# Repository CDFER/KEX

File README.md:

# Currently not maintained or tested, use at your own risk

## KEX a Rapid Deployment ESP32 Board
A fast and feature-rich implementation of an ESP32 board with NeoPixel Led (WS2812B, WS2811, SK6812), I2S (Digital microphone) and I2C outputs.

## ⚙️ Features
- Supports USB C to USB C cables at 5V 3A 
- 3 Capacitive Touch Buttons
- Designed for PCB Assembly by JLCPCB 
- 3A Resettable Fuse on both the 3.3v and 5v Rails
- Programming using the CH340-c IC
- Electrostatic Discharge Protection on USB and LED Output
- Auto Reset for easy programming
- Solder Pad connections with Strain relief slots 
- High-Speed Bi-Directional Level shifted I2S and I2C ports using BSS138 like [Adafruit](https://www.adafruit.com/product/757)
- Cuttable solder pads to select between 3.3v and 5v level shifting
- LED indicators on all outputs and inputs
- Easy soldering of led strips directly to the PCB with Strain Releaf slots

## 📲 Quickstart
1. Solder the ESP32 to the footprint on the PCB

2. Connect up to 120 NeoPixels (WS2812B, WS2811, SK6812) to the output pads (IO2). 
3. Install the CH340 Drivers from [Sparkfun](https://learn.sparkfun.com/tutorials/how-to-install-ch340-drivers/all)
4. Flash the software to your ESP module! There are two options for this step:
  
&nbsp;&nbsp;&nbsp;&nbsp;&nbsp;&nbsp;[I just want to use WLED! (install release binary)](https://install.wled.me/)

&nbsp;&nbsp;&nbsp;&nbsp;&nbsp;&nbsp;[I want to modify WLED (compile from source code)](https://kno.wled.ge/advanced/compiling-wled/)

&nbsp;&nbsp;&nbsp;&nbsp;&nbsp;&nbsp;If set up correctly, the first thirty LEDs will light up!

5. Use a Computer/Phone to connect to the Wife named: WLED-AP using the password wled1234.

6. Click on the cog icon to edit settings like connecting the module to your home WiFi.
7. Upload Config File (Coming soon...)

## 💾 Pinout
Pin | IO2 | IO4 | IO14 | IO15 | IO21 | IO22 | IO27 | IO32 | IO33 | IO36
--- | --- | --- | --- |--- |--- |--- |--- |--- |--- |---
Usage | LED Output | Down Touch Pad | SCK | WS | SDA | SCL | Middle Touch Pad | SD |  Up Touch Pad | Analog Input 
LED | Yellow | | White | White | Red | Green | | White | | |
Level Shifted | | |✅|✅|✅|✅| |✅| 

## ✌️ Other

[Licensed under the MIT license](https://github.com/git/git-scm.com/blob/main/MIT-LICENSE.txt)

Designed by Chris Dirks (@CD_FER)

You can also send me emails to [cdirksfer@gmail.com](mailto:dev.cdirksfer@gmail.com), but please only do so if you want to talk to me privately.

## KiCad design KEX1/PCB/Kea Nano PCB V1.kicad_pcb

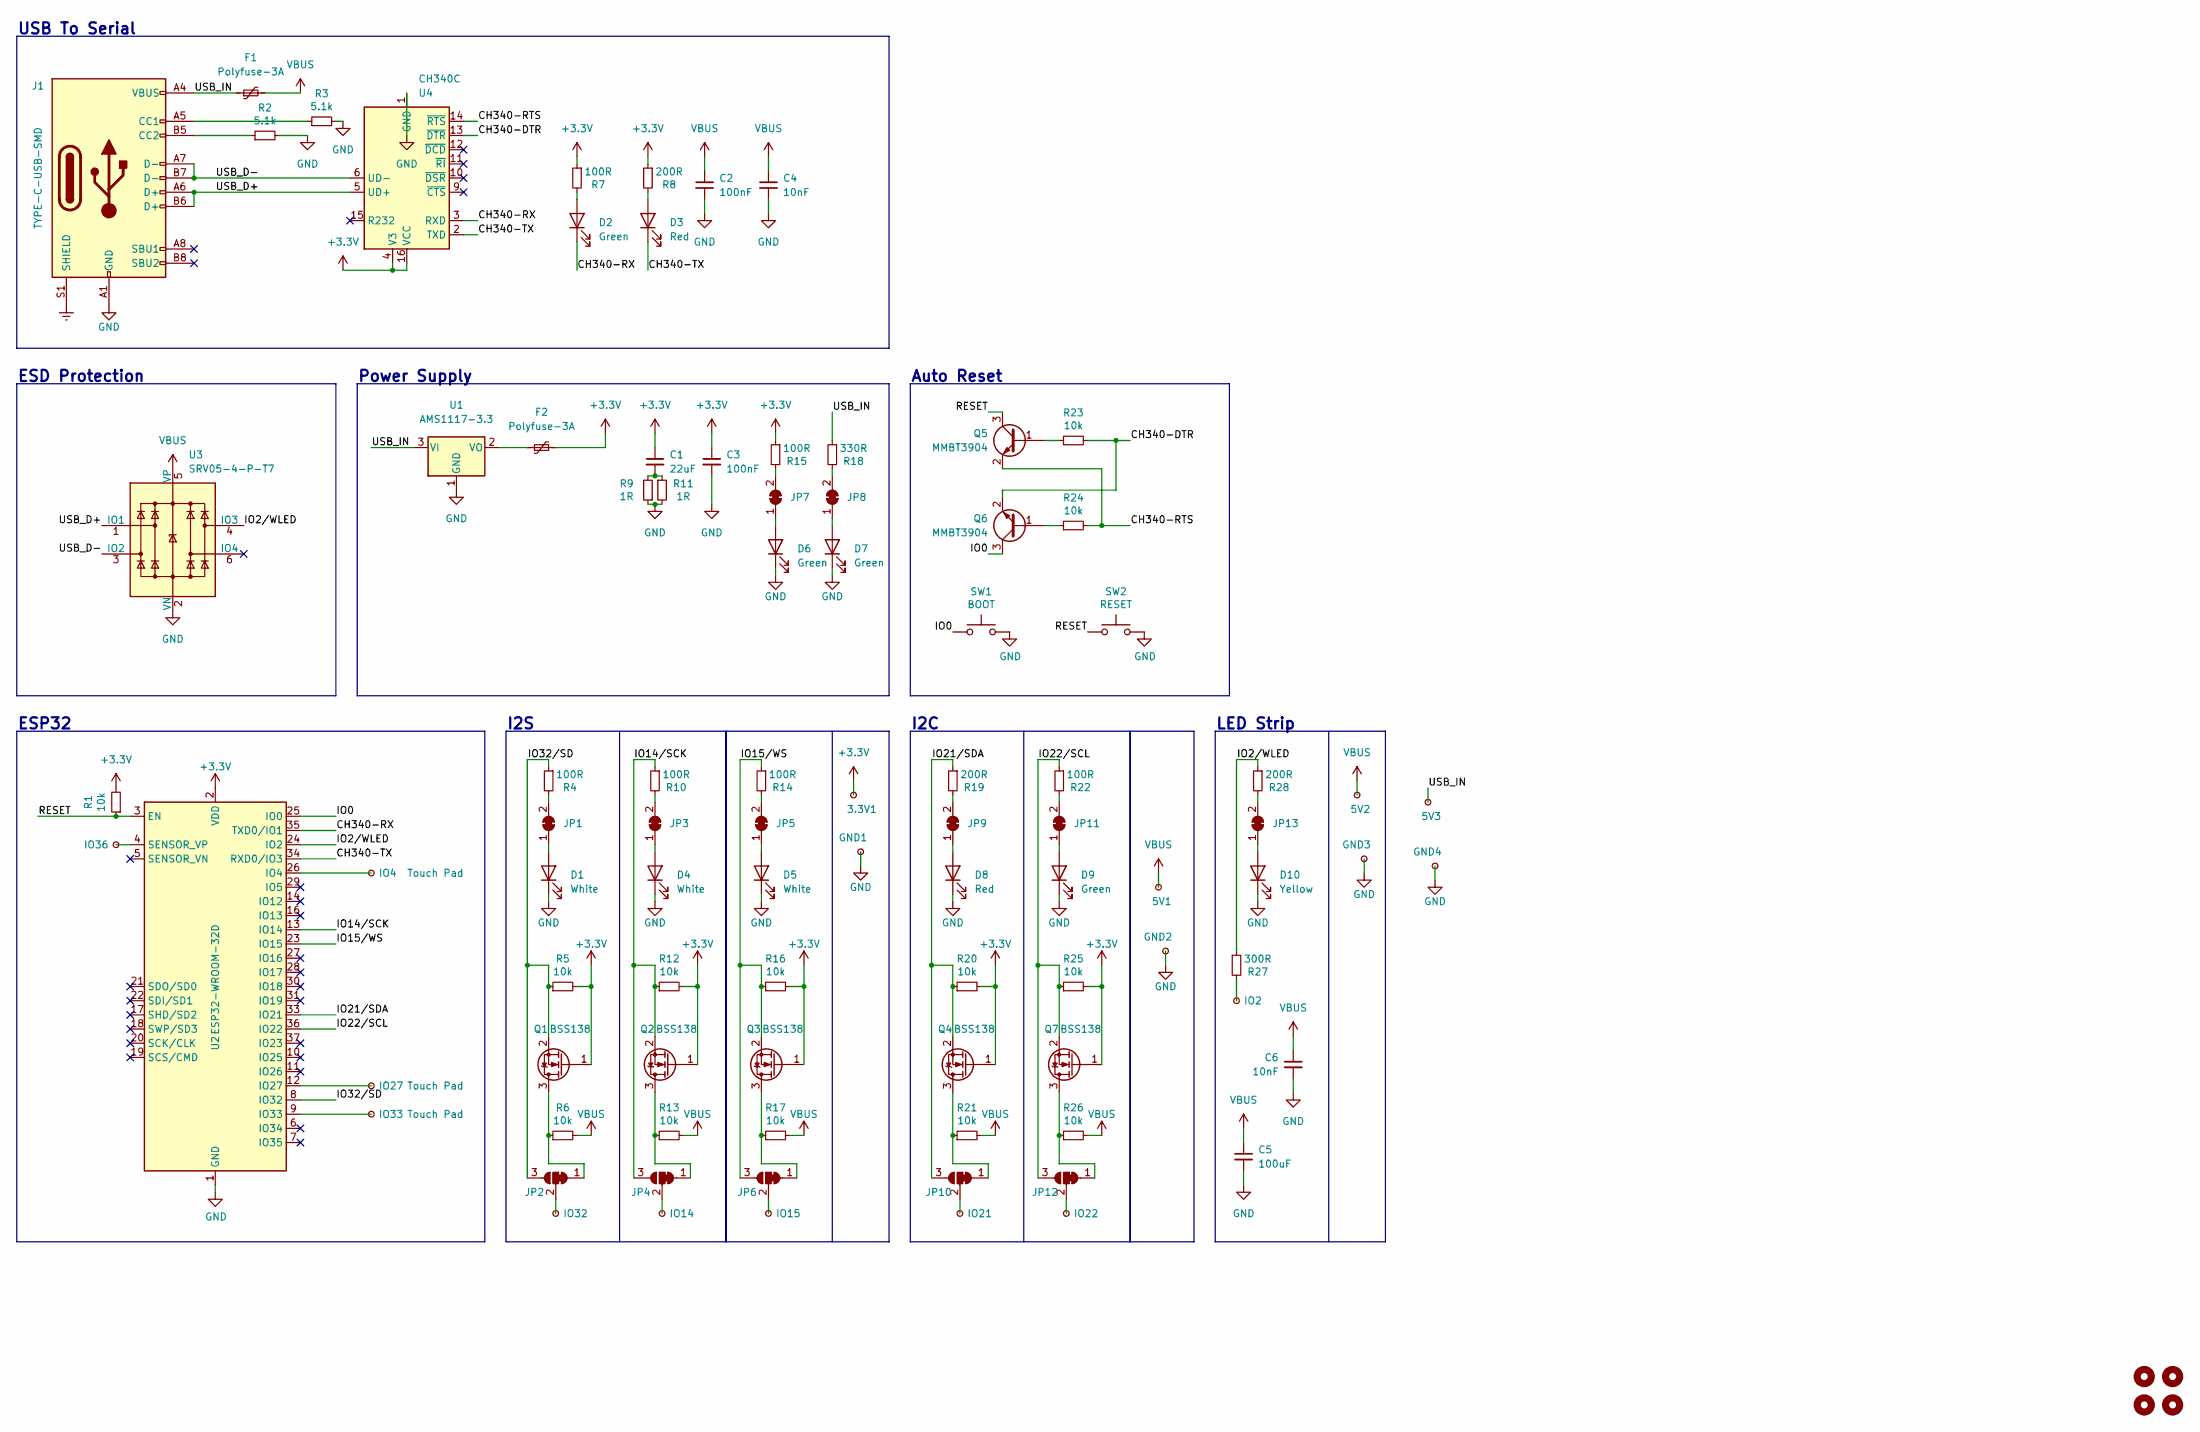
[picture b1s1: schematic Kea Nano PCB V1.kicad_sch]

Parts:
3.3V1, 5V1, 5V2, 5V3: IO; IO Pad
C1: 22uF; C_1206_3216Metric; LCSC C5672
C2, C3: 100nF; C_0402_1005Metric; LCSC C1525
C4, C6: 10nF; C_0402_1005Metric; LCSC C15195
C5: 100uF; C_1206_3216Metric; LCSC C15008
D1, D4, D5: White; LED_0603_1608Metric; LCSC C2290
D2, D6, D7, D9: Green; LED_0603_1608Metric; LCSC C72043
D3, D8: Red; LED_0603_1608Metric; LCSC C2286
D10: Yellow; LED_0603_1608Metric; LCSC C72038
F1, F2: Polyfuse-3A; Fuse_1206_3216Metric; LCSC C516068
GND1, GND2, GND3, GND4: IO; IO Pad
H1, H2, H3, H4: MountingHole; MountingHole_3.2mm_M3_DIN965
IO2, IO14, IO15, IO21, IO22, IO32, IO36: IO; IO Pad
IO4: Touch Pad; Touch Pad ST
IO27, IO33: Touch Pad
J1: TYPE-C-USB-SMD; USB_C_Receptacle_XKB_U262-16XN-4BVC11; LCSC C167321
JP1, JP3, JP5, JP7, JP8, JP9, JP11, JP13: SolderJumper_2_Bridged; SolderJumper-2_P1.3mm_Bridged_RoundedPad1.0x1.5mm
JP2, JP4, JP6, JP10, JP12: SolderJumper_3_Bridged12; SolderJumper-3_P1.3mm_Bridged12_RoundedPad1.0x1.5mm
Q1, Q2, Q3, Q4, Q7: BSS138; SOT-23; LCSC C78284
Q5, Q6: MMBT3904; SOT-23; LCSC C20526
R1, R5, R6, R12, R13, R16, R17, R20, R21, R23, R24, R25, R26: 10k; R_0402_1005Metric; LCSC C25744
R2, R3: 5.1k; R_0402_1005Metric; LCSC C25905
R4, R7, R10, R14, R15, R22: 100R; R_0402_1005Metric; LCSC C25076
R8, R19, R28: 200R; R_0402_1005Metric; LCSC C25087
R9, R11: 1R; R_0402_1005Metric; LCSC C25086
R18: 330R; R_0402_1005Metric; LCSC C25104
R27: 300R; R_0402_1005Metric; LCSC C25102
SW1: BOOT; TS-1187A-B-A-B; LCSC C318884
SW2: RESET; TS-1187A-B-A-B; LCSC C318884
U1: AMS1117-3.3; SOT-223; LCSC C6186
U2: ESP32-WROOM-32D; ESP32-WROOM-32
U3: SRV05-4-P-T7; SOT-23-6; LCSC C85364
U4: CH340C; SOP-16_3.9x9.9mm_P1.27mm; LCSC C84681

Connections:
+3V3: 3.3V1.1, C1.1, C3.1, F2.2, Q1.1 (G), Q2.1 (G), Q3.1 (G), Q4.1 (G), Q7.1 (G), R1.2, R5.2, R7.1, R8.1, R12.2, R15.1, R16.2, R20.2, R25.2, U2.2 (VDD), U4.4 (V3), U4.16 (VCC)
/CH340-DTR: Q6.2 (E), R23.2, U4.13 (~DTR)
/CH340-RTS: Q5.2 (E), R24.2, U4.14 (~RTS)
/CH340-RX: D2.1 (K), U2.35 (TXD0/IO1), U4.3 (RXD)
/CH340-TX: D3.1 (K), U2.34 (RXD0/IO3), U4.2 (TXD)
/IO0: Q6.3 (C), SW1.1, U2.25 (IO0)
/IO2/WLED: R27.1, R28.1, U2.24 (IO2), U3.4 (IO3)
/IO14/SCK: JP4.3 (B), Q2.2 (S), R10.1, R12.1, U2.13 (IO14)
/IO15/WS: JP6.3 (B), Q3.2 (S), R14.1, R16.1, U2.23 (IO15)
/IO21/SDA: JP10.3 (B), Q4.2 (S), R19.1, R20.1, U2.33 (IO21)
/IO22/SCL: JP12.3 (B), Q7.2 (S), R22.1, R25.1, U2.36 (IO22)
/IO32/SD: JP2.3 (B), Q1.2 (S), R4.1, R5.1, U2.8 (IO32)
/RESET: Q5.3 (C), R1.1, SW2.1, U2.3 (EN)
/USB_D+: J1.A6 (D+), J1.B6 (D+), U3.1 (IO1), U4.5 (UD+)
/USB_D-: J1.A7 (D-), J1.B7 (D-), U3.3 (IO2), U4.6 (UD-)
/USB_IN: 5V3.1, F1.1, J1.A4 (VBUS), J1.A9 (VBUS), J1.B4 (VBUS), J1.B9 (VBUS), R18.1, U1.3 (VI); also elsewhere on the board
GND: C2.2, C3.2, C4.2, C5.2, C6.2, D1.1 (K), D4.1 (K), D5.1 (K), D6.1 (K), D7.1 (K), D8.1 (K), D9.1 (K), D10.1 (K), GND1.1, GND2.1, GND3.1, GND4.1, J1.A1 (GND), J1.A12 (GND), J1.B1 (GND), J1.B12 (GND), R2.2, R3.2, R9.1, R11.2, SW1.2, SW2.2, U1.1 (GND), U2.1 (GND), U2.15 (GND), U2.38 (GND), U2.39 (GND), U3.2 (VN), U4.1 (GND)
unnamed: C1.2, R9.2, R11.1
unnamed: D1.2 (A), JP1.1 (A)
unnamed: D2.2 (A), R7.2
unnamed: D3.2 (A), R8.2
unnamed: D4.2 (A), JP3.1 (A)
unnamed: D5.2 (A), JP5.1 (A)
unnamed: D6.2 (A), JP7.1 (A)
unnamed: D7.2 (A), JP8.1 (A)
unnamed: D8.2 (A), JP9.1 (A)
unnamed: D9.2 (A), JP11.1 (A)
unnamed: D10.2 (A), JP13.1 (A)
unnamed: F2.1, U1.2 (VO)
unnamed: IO2.1, R27.2
unnamed: IO4.1, U2.26 (IO4)
unnamed: IO14.1, JP4.2 (C)
unnamed: IO15.1, JP6.2 (C)
unnamed: IO21.1, JP10.2 (C)
unnamed: IO22.1, JP12.2 (C)
unnamed: IO27.1, U2.12 (IO27)
unnamed: IO32.1, JP2.2 (C)
unnamed: IO33.1, U2.9 (IO33)
unnamed: IO36.1, U2.4 (SENSOR_VP)
unnamed: J1.A5 (CC1), R3.1
unnamed: J1.B5 (CC2), R2.1
unnamed: JP1.2 (B), R4.2
unnamed: JP2.1 (A), Q1.3 (D), R6.1
unnamed: JP3.2 (B), R10.2
unnamed: JP4.1 (A), Q2.3 (D), R13.1
unnamed: JP5.2 (B), R14.2
unnamed: JP6.1 (A), Q3.3 (D), R17.1
unnamed: JP7.2 (B), R15.2
unnamed: JP8.2 (B), R18.2
unnamed: JP9.2 (B), R19.2
unnamed: JP10.1 (A), Q4.3 (D), R21.1
unnamed: JP11.2 (B), R22.2
unnamed: JP12.1 (A), Q7.3 (D), R26.1
unnamed: JP13.2 (B), R28.2
unnamed: Q5.1 (B), R23.1
unnamed: Q6.1 (B), R24.1
VBUS: 5V1.1, 5V2.1, C2.1, C4.1, C5.1, C6.1, F1.2, R6.2, R13.2, R17.2, R21.2, R26.2, U3.5 (VP); also elsewhere on the board

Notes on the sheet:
ESP32
I2C
USB To Serial
ESD Protection
I2S
LED Strip
Auto Reset
Power Supply

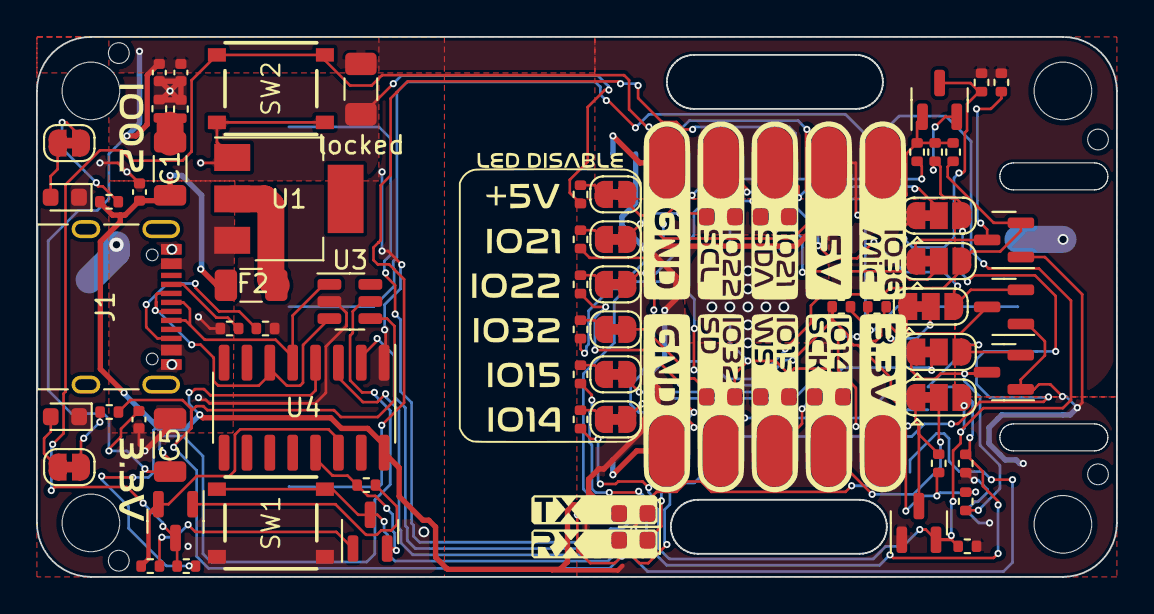
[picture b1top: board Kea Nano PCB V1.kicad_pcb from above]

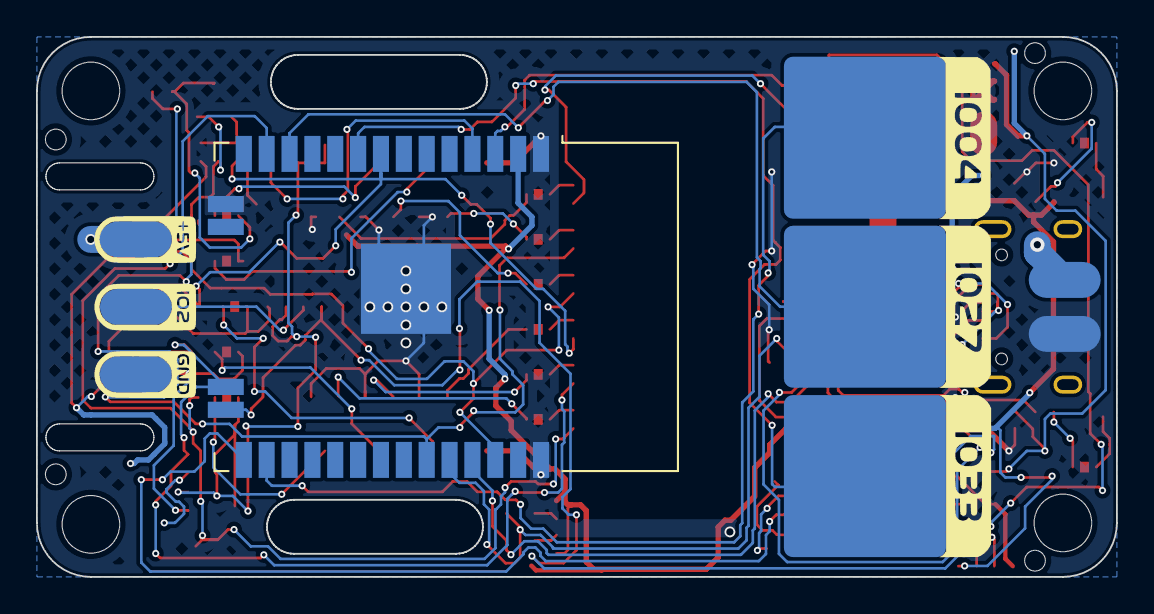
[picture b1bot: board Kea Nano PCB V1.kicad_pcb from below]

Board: 2 copper layers, 60.0 x 30.0 mm, 95 parts (9 on the bottom side), 57 nets.

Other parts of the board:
locked: Polyfuse-3A; Fuse_1206_3216Metric

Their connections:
/USB_IN: locked.1; also elsewhere on the board
VBUS: locked.2; also elsewhere on the board

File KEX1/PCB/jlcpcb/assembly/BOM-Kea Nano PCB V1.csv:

Comment,Designator,Footprint,LCSC
100uF,C5,C_1206_3216Metric,C15008
10nF,"C4,C6",C_0402_1005Metric,C15195
100nF,"C2,C3",C_0402_1005Metric,C1525
TYPE-C-USB-SMD,J1,USB_C_Receptacle_XKB_U262-16XN-4BVC11,C167321
MMBT3904,"Q5,Q6",SOT-23,C20526
Red,"D3,D8",LED_0603_1608Metric,C2286
White,"D1,D4,D5",LED_0603_1608Metric,C2290
100R,"R10,R14,R15,R22,R4,R7",R_0402_1005Metric,C25076
1R,"R11,R9",R_0402_1005Metric,C25086
200R,"R19,R28,R8",R_0402_1005Metric,C25087
300R,R27,R_0402_1005Metric,C25102
330R,R18,R_0402_1005Metric,C25104
10k,"R1,R12,R13,R16,R17,R20,R21,R23,R24,R25,R26,R5,R6",R_0402_1005Metric,C25744
5.1k,"R2,R3",R_0402_1005Metric,C25905
BOOT,"SW1,SW2",TS-1187A-B-A-B,C318884
Polyfuse-3A,"F1,F2",Fuse_1206_3216Metric,C516068
22uF,C1,C_1206_3216Metric,C5672
AMS1117-3.3,U1,SOT-223,C6186
Yellow,D10,LED_0603_1608Metric,C72038
Green,"D2,D6,D7,D9",LED_0603_1608Metric,C72043
BSS138,"Q1,Q2,Q3,Q4,Q7",SOT-23,C78284
CH340C,U4,SOP-16_3.9x9.9mm_P1.27mm,C84681
SRV05-4-P-T7,U3,SOT-23-6,C85364

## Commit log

2022-04-15 Tidy up and add ReadMe Images
